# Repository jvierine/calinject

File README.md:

# Calinject

GPS-timed calibration bursts for SDR recordings: recover sample timing, estimate sample rate, and track frequency drift.

- **10 MHz harmonic comb**, with calibration harmonics through 70 MHz.
- **100 µs bursts by default**; pulse length and level adjustable over USB.
- Separate **10 MHz and 1 PPS SMA outputs**.
- **USB-C power**, firmware loading and status. Runs without a computer after programming; saved settings restore at startup.
- Four-layer, 90 × 65 mm PCB and a printable case with horizontal SMA ports.

Connect **antenna bias board → RF IN → TO SDR → receiver**. Add an active GPS antenna and 5 V USB-C power. The receiver path blocks DC and is specified for **0.5–70 MHz**, with about **3.2 dB loss**. Calibration leakage toward the antenna is finite; it must be measured on the first board.

Parts and board cost about **$80 per unit in small quantities**.

**Simulation, not measured performance:** longer bursts improve frequency estimation in the modeled receivers. Timing assumes known fixed delays and correctly associated UTC seconds. [Figures and assumptions](docs/figures.md).

[Download files](https://github.com/jvierine/calinject/releases) · [USB programming](firmware/README.md) · [Controls and LED](docs/operation.md) · [Print the case](mechanical/README.md) · [Hardware acceptance](docs/acceptance.md)

[Design](docs/design.md) · [Simulation details](docs/end-to-end.md) · [CAD/build](docs/build.md) · [Assembly](manufacturing/ASSEMBLY.md) · [Cost](docs/cost.md)

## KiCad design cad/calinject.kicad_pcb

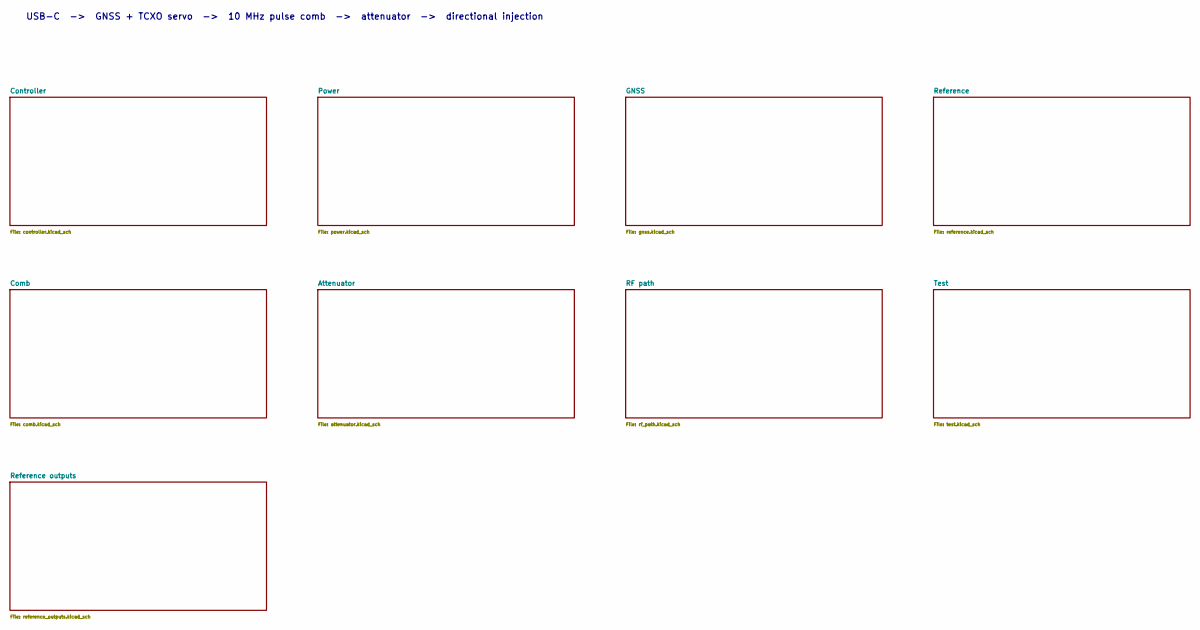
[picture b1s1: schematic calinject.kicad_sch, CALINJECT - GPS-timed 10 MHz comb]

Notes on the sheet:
USB-C -> GNSS + TCXO servo -> 10 MHz pulse comb -> attenuator -> directional injection

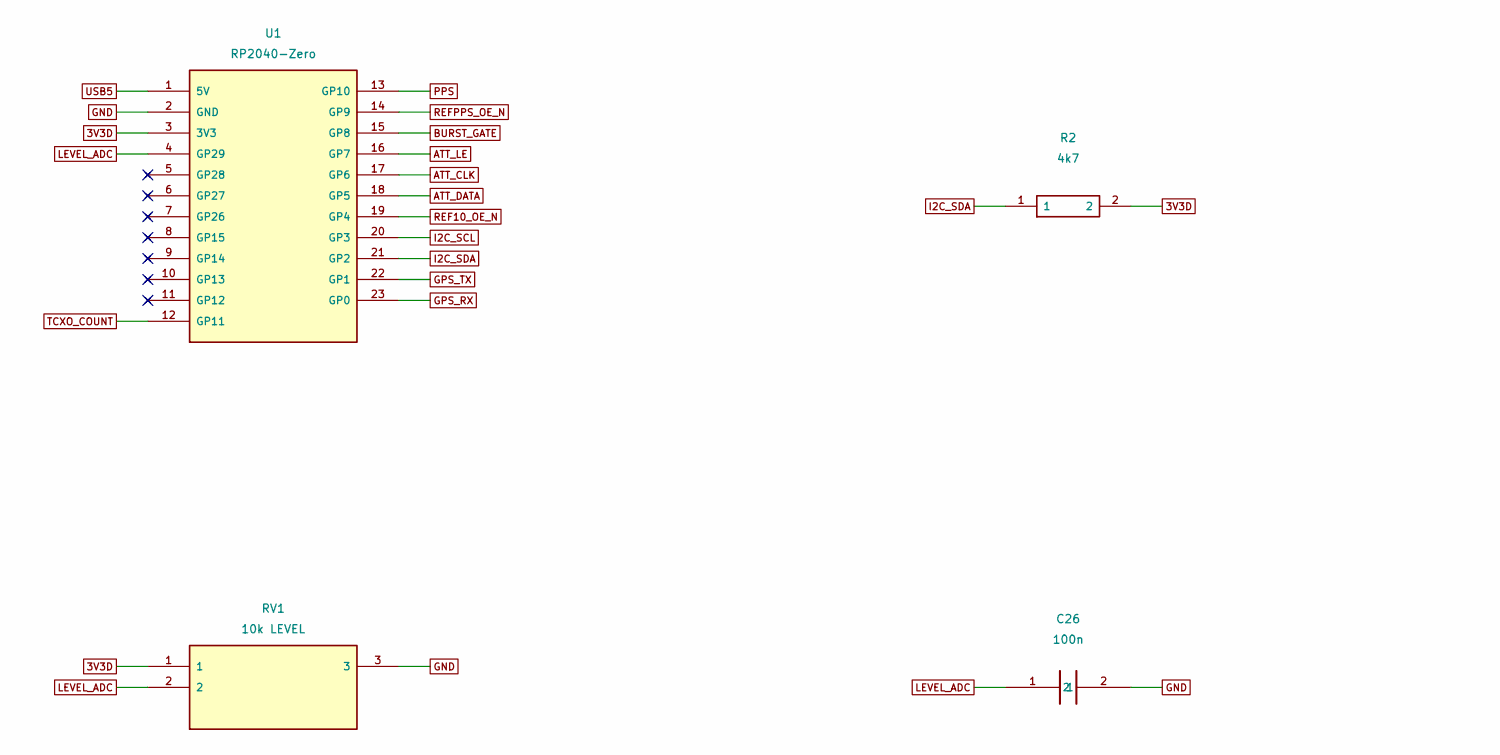
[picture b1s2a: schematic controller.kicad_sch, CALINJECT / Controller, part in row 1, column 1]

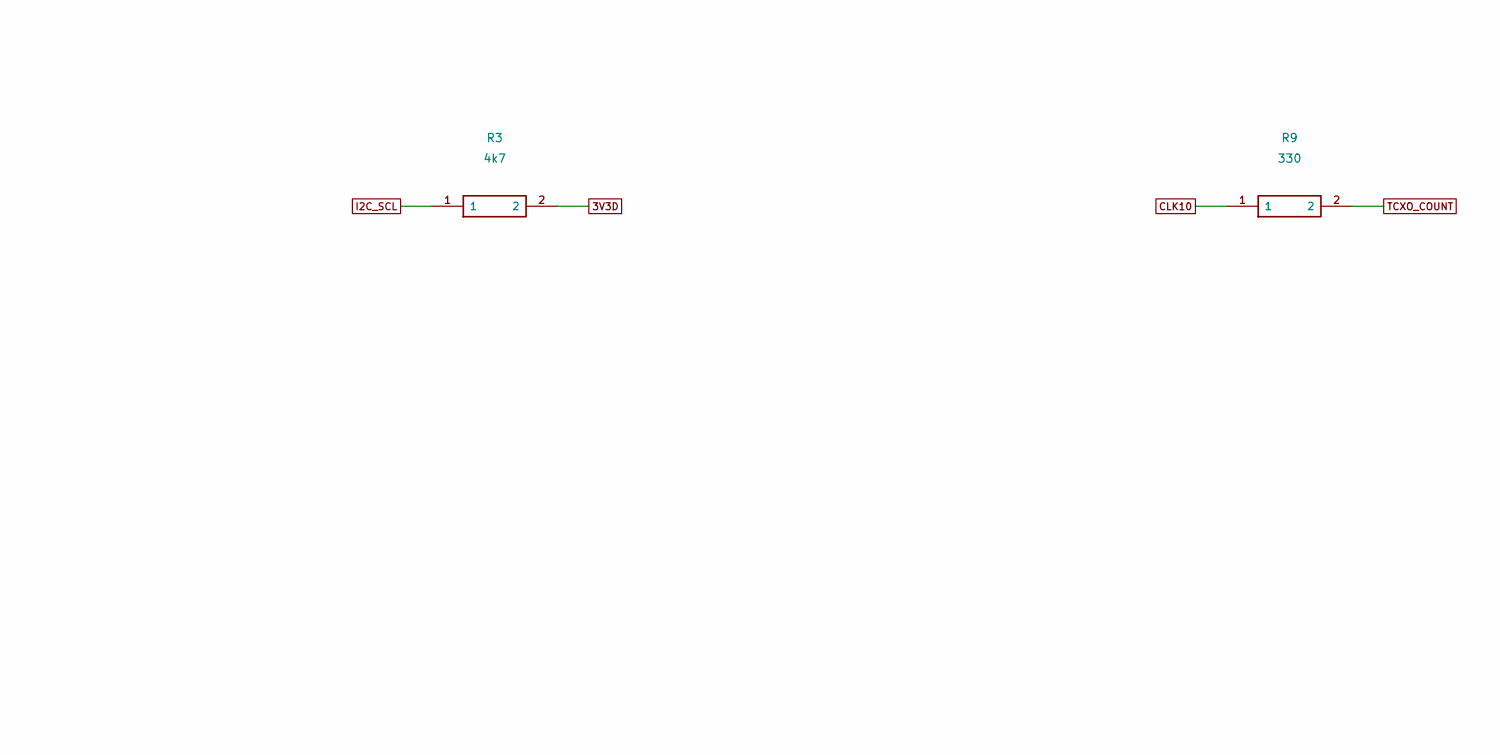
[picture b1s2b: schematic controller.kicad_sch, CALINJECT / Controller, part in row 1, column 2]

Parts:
C26: 100n; C_0603_C26
R2: 4k7; R_0603_R2
R3: 4k7; R_0603_R3
R9: 330; R_0603_R9
RV1: 10k LEVEL; Bourns_3362P_RV1
U1: RP2040-Zero; RP2040_Zero_U1

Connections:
3V3D: R2.2, R3.2, RV1.1, U1.3 (3V3)
ATT_CLK: U1.17 (GP6); also elsewhere on the board
ATT_DATA: U1.18 (GP5); also elsewhere on the board
ATT_LE: U1.16 (GP7); also elsewhere on the board
BURST_GATE: U1.15 (GP8); also elsewhere on the board
CLK10: R9.1; also elsewhere on the board
GND: C26.2, RV1.3, U1.2 (GND); also elsewhere on the board
GPS_RX: U1.23 (GP0); also elsewhere on the board
GPS_TX: U1.22 (GP1); also elsewhere on the board
I2C_SCL: R3.1, U1.20 (GP3); also elsewhere on the board
I2C_SDA: R2.1, U1.21 (GP2); also elsewhere on the board
LEVEL_ADC: C26.1, RV1.2, U1.4 (GP29)
PPS: U1.13 (GP10); also elsewhere on the board
REF10_OE_N: U1.19 (GP4); also elsewhere on the board
REFPPS_OE_N: U1.14 (GP9); also elsewhere on the board
TCXO_COUNT: R9.2, U1.12 (GP11); also elsewhere on the board
USB5: U1.1 (5V); also elsewhere on the board

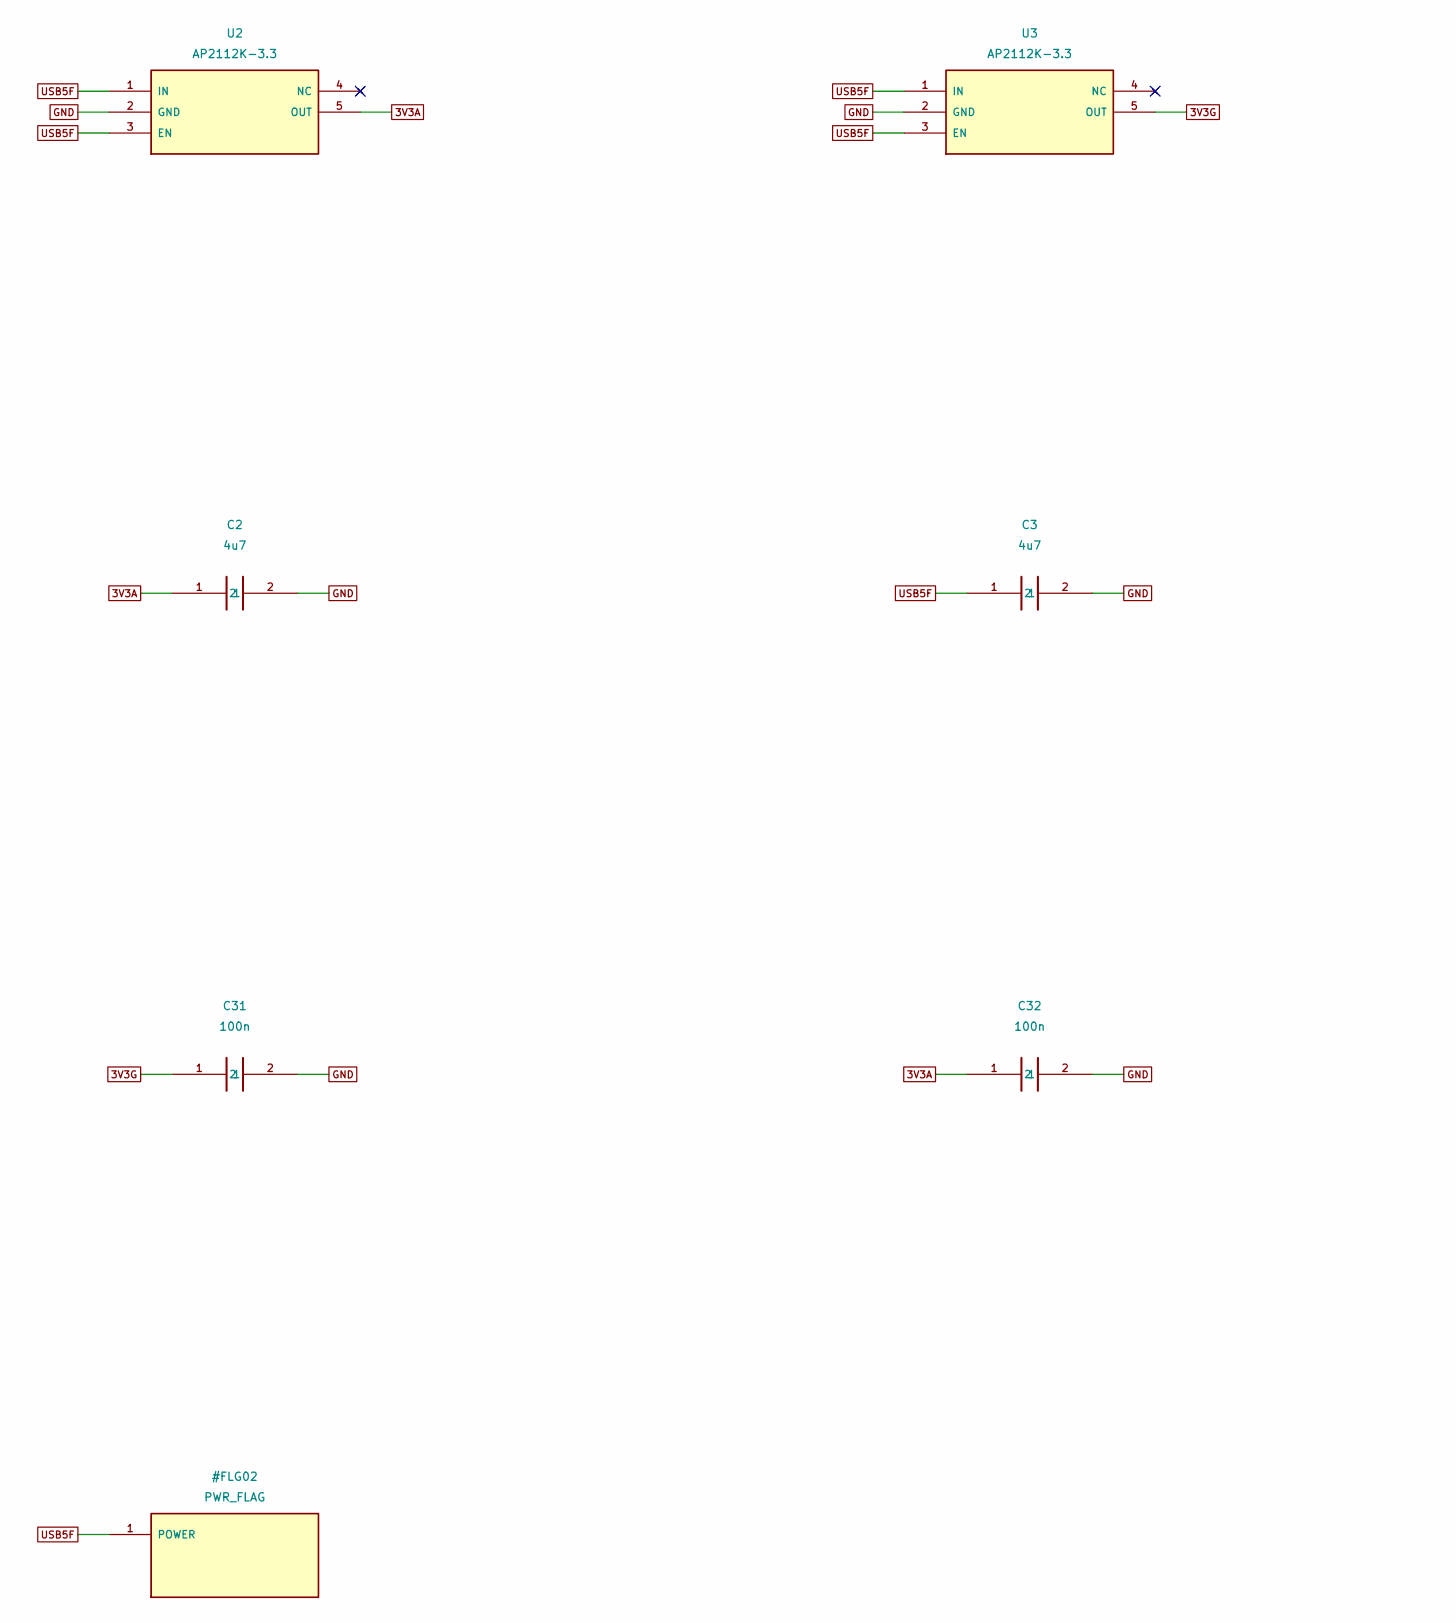
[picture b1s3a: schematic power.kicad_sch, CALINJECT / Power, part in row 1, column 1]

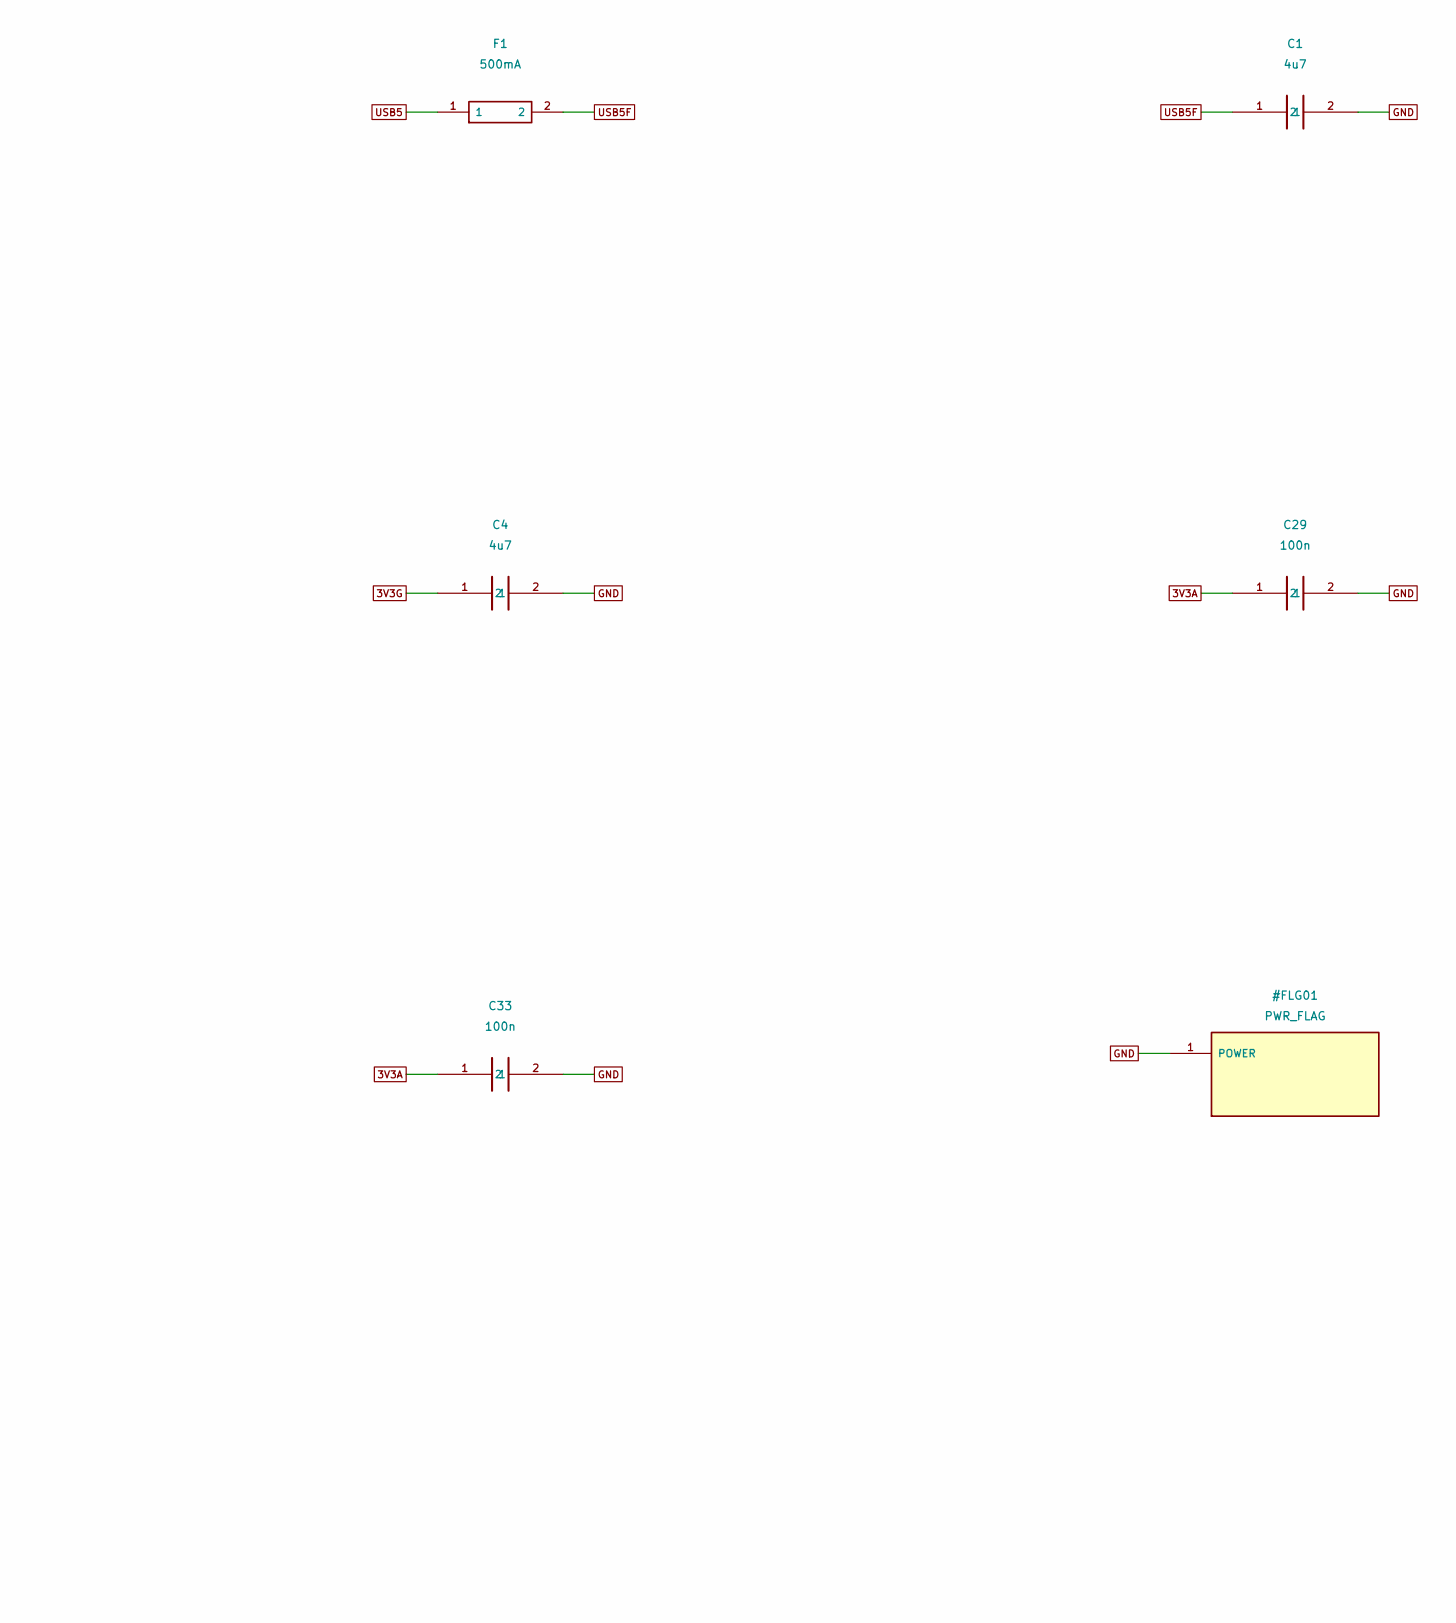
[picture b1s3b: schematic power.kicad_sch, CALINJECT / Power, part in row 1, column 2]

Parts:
C1: 4u7; C_0603_C1
C2: 4u7; C_0603_C2
C3: 4u7; C_0603_C3
C4: 4u7; C_0603_C4
C29: 100n; C_0603_C29
C31: 100n; C_0603_C31
C32: 100n; C_0603_C32
C33: 100n; C_0603_C33
F1: 500mA; F_1206_F1
U2: AP2112K-3.3; SOT23_5_U2
U3: AP2112K-3.3; SOT23_5_U3

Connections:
3V3A: C2.1, C29.1, C32.1, C33.1, U2.5 (OUT); also elsewhere on the board
3V3G: C4.1, C31.1, U3.5 (OUT); also elsewhere on the board
GND: C1.2, C2.2, C3.2, C4.2, C29.2, C31.2, C32.2, C33.2, U2.2 (GND), U3.2 (GND); also elsewhere on the board
USB5: F1.1; also elsewhere on the board
USB5F: C1.1, C3.1, F1.2, U2.1 (IN), U2.3 (EN), U3.1 (IN), U3.3 (EN)

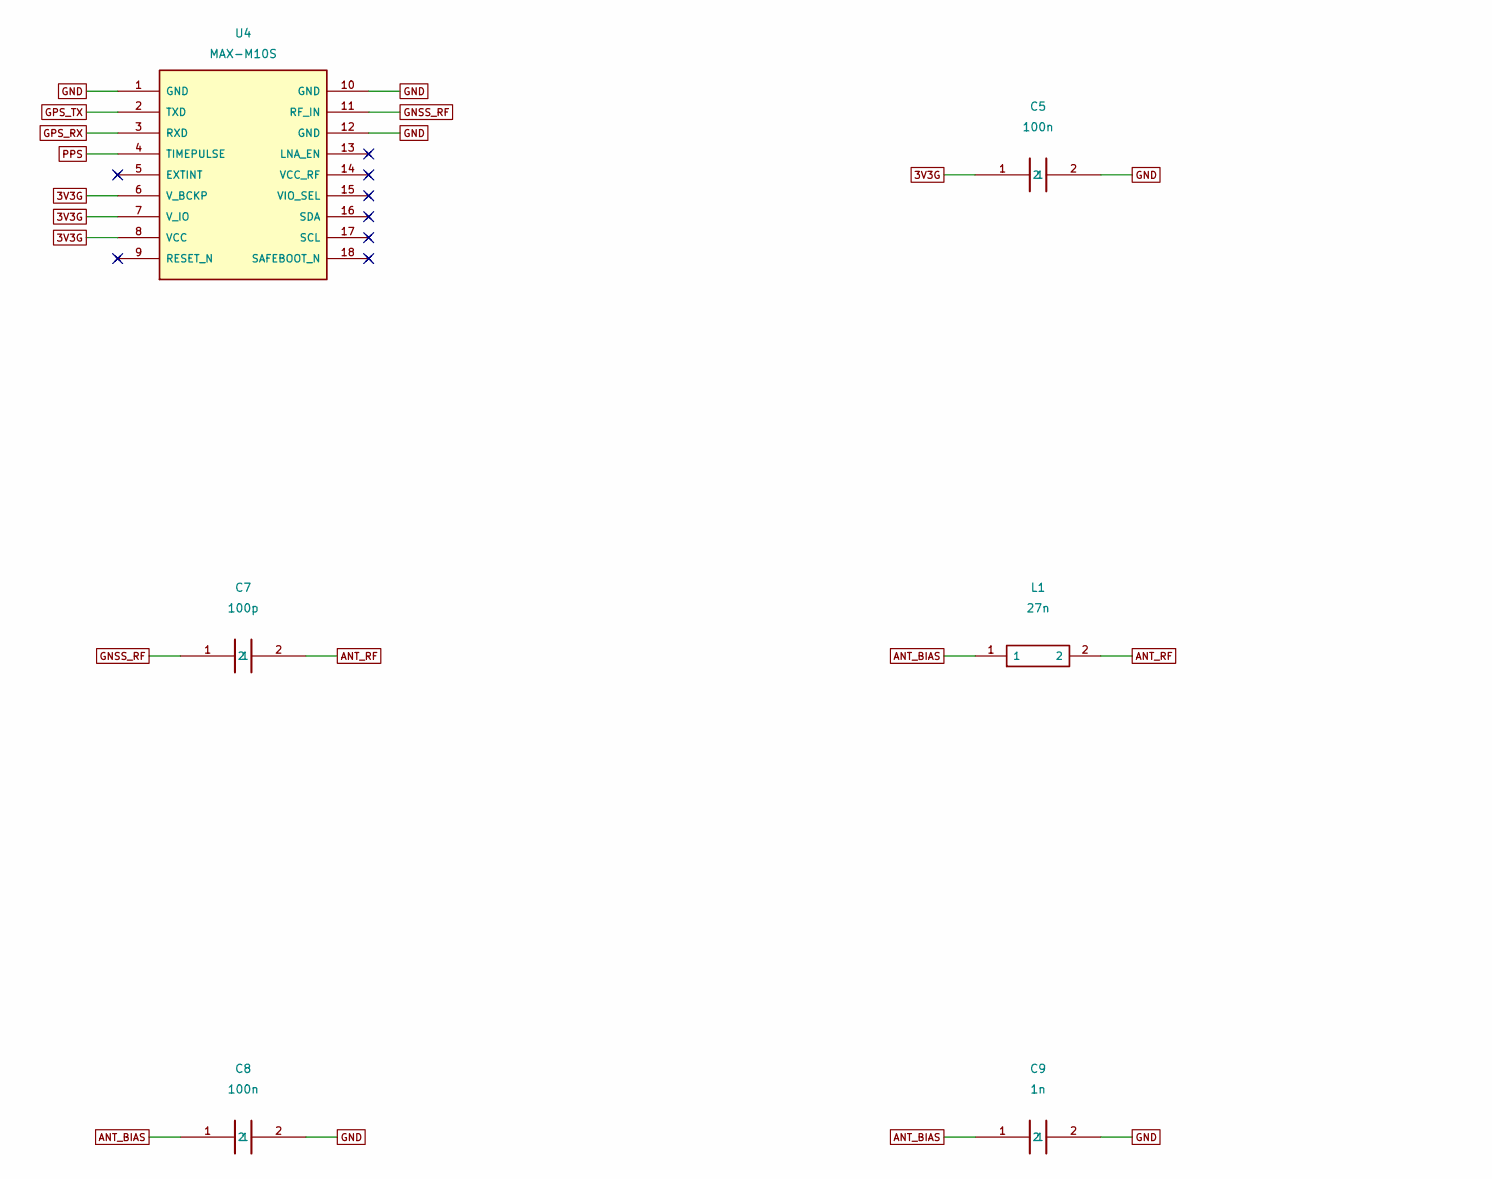
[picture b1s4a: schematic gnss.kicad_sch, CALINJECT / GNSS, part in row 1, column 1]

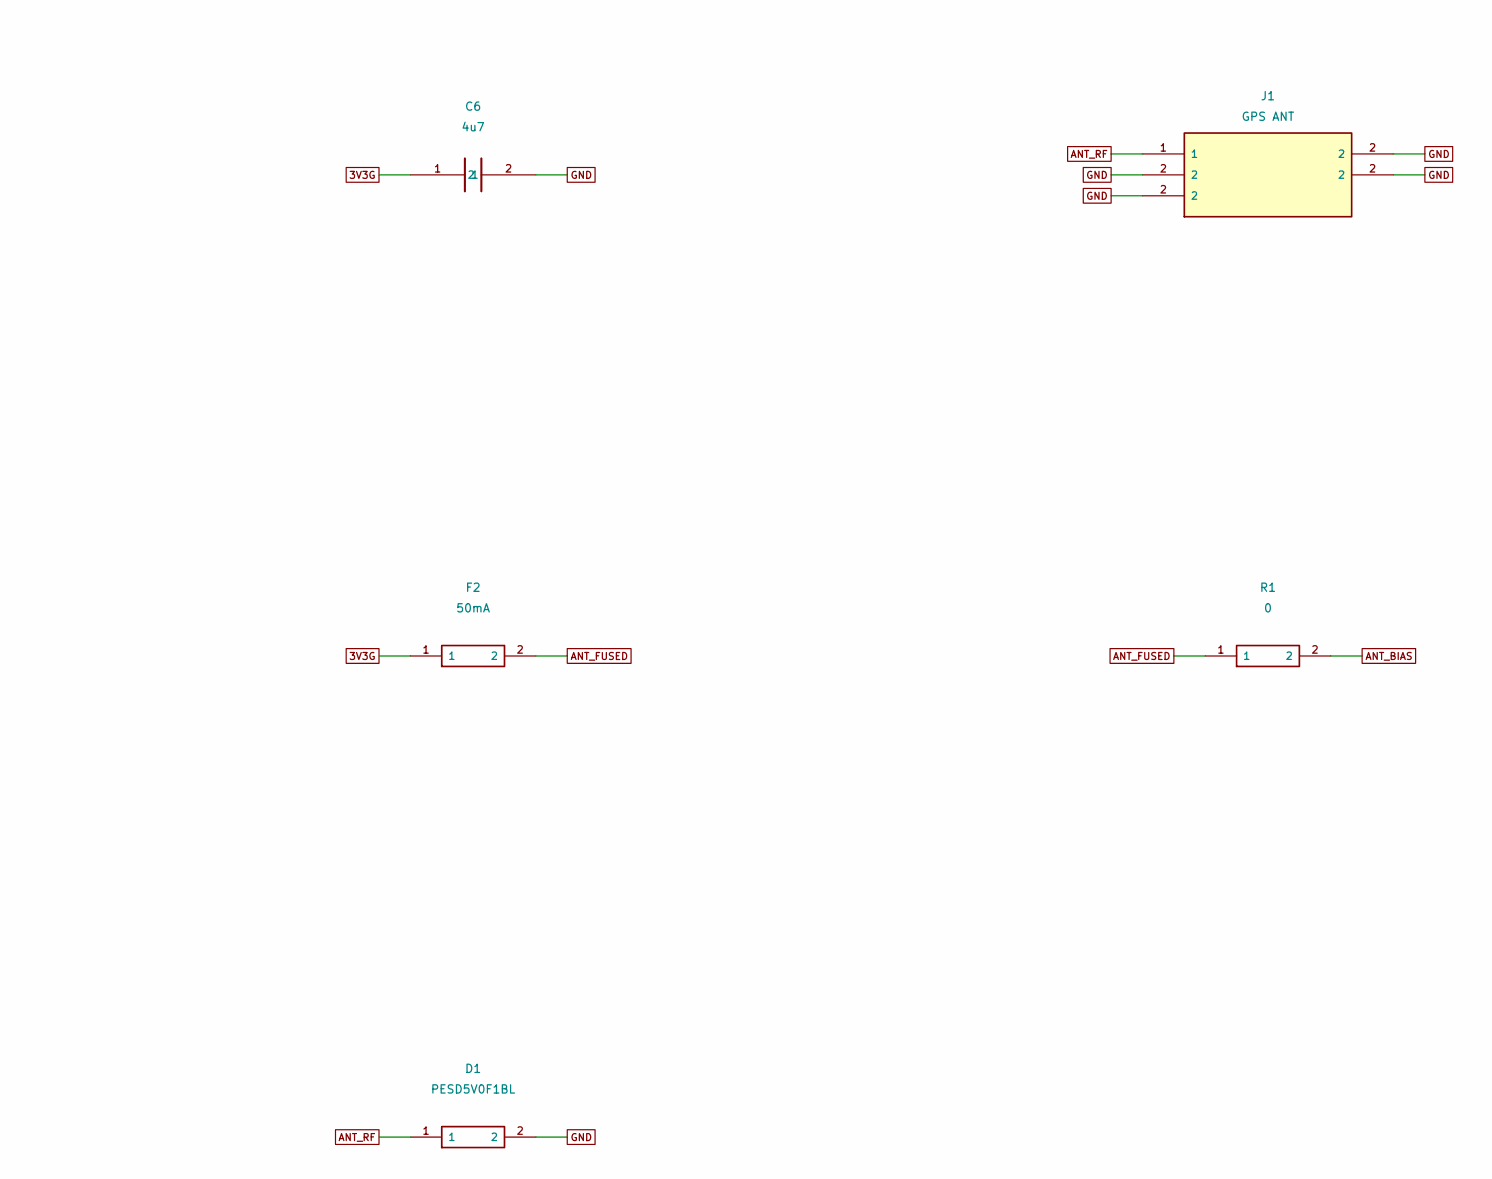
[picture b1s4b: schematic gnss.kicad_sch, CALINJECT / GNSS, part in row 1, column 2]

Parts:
C5: 100n; C_0603_C5
C6: 4u7; C_0603_C6
C7: 100p; C_0402_C7
C8: 100n; C_0603_C8
C9: 1n; C_0603_C9
D1: PESD5V0F1BL; DFN1006_2_D1
F2: 50mA; F_1206_F2
J1: GPS ANT; SMA_KWE_RA_J1
L1: 27n; L_0402_L1
R1: 0; R_0603_R1
U4: MAX-M10S; MAX_M10S_U4

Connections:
3V3G: C5.1, C6.1, F2.1, U4.6 (V_BCKP), U4.7 (V_IO), U4.8 (VCC); also elsewhere on the board
ANT_BIAS: C8.1, C9.1, L1.1, R1.2
ANT_FUSED: F2.2, R1.1
ANT_RF: C7.2, D1.1, J1.1, L1.2
GND: C5.2, C6.2, C8.2, C9.2, D1.2, J1.2, U4.1 (GND), U4.10 (GND), U4.12 (GND); also elsewhere on the board
GNSS_RF: C7.1, U4.11 (RF_IN)
GPS_RX: U4.3 (RXD); also elsewhere on the board
GPS_TX: U4.2 (TXD); also elsewhere on the board
PPS: U4.4 (TIMEPULSE); also elsewhere on the board

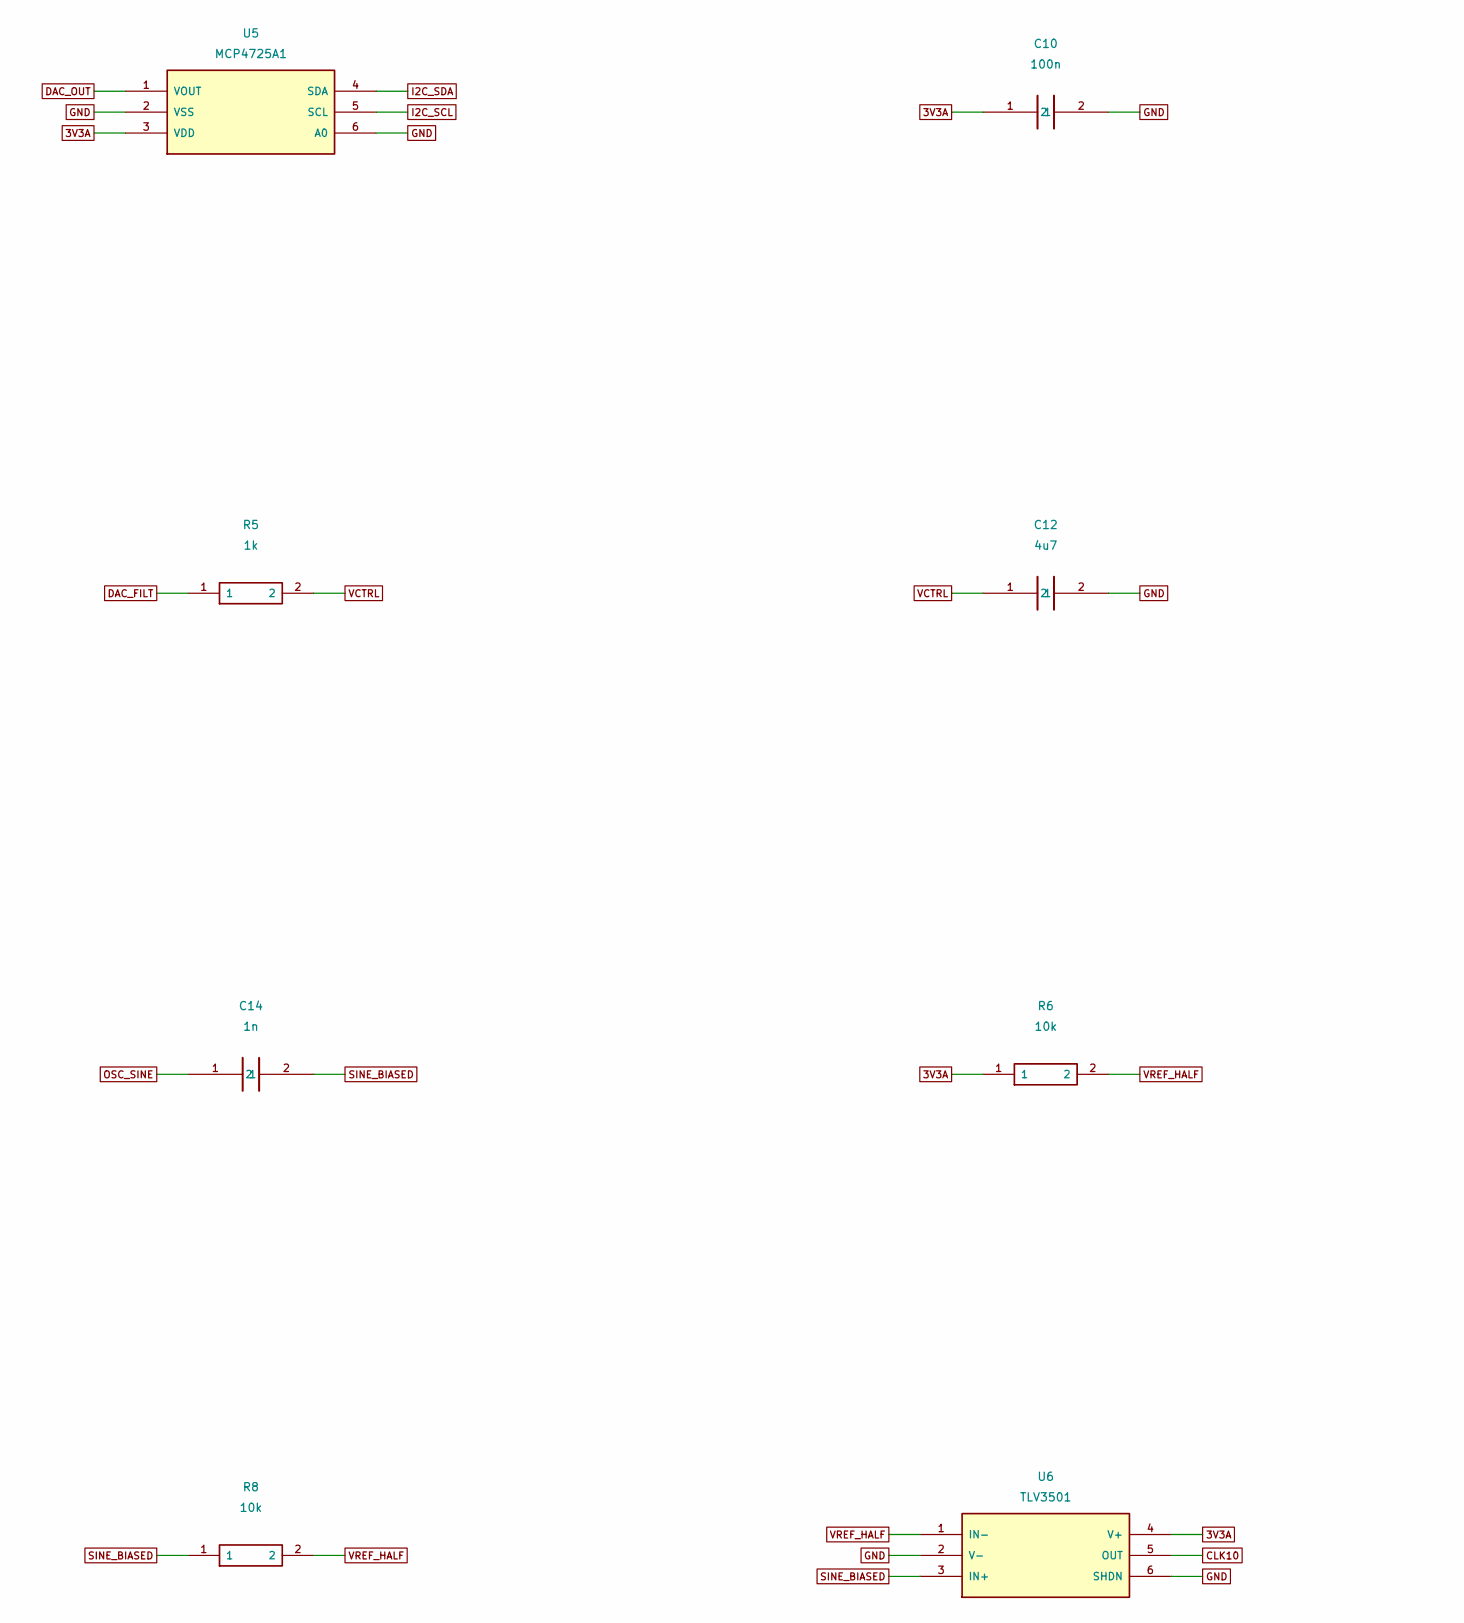
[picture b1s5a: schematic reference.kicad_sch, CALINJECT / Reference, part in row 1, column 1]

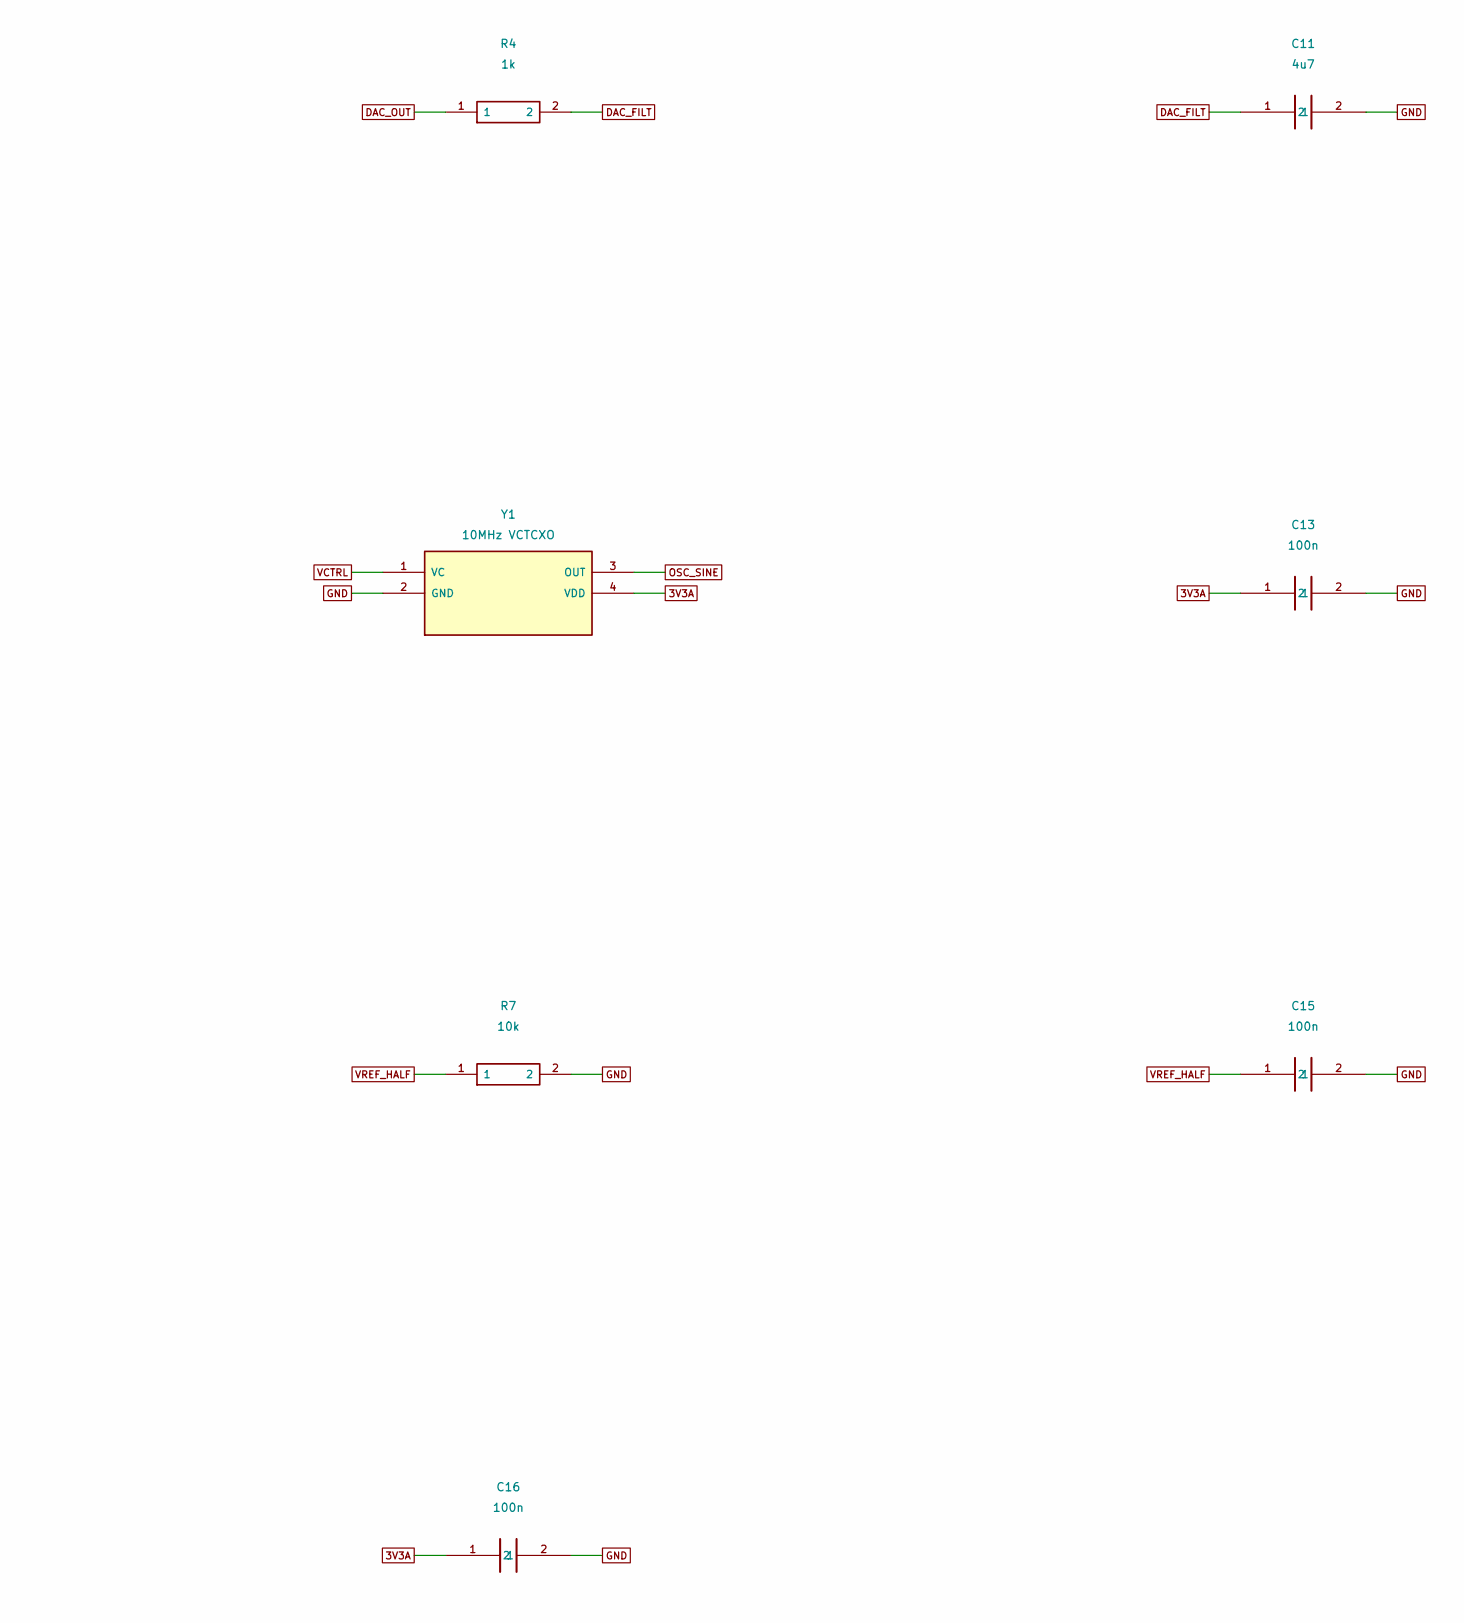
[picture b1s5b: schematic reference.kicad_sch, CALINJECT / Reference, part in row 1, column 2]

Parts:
C10: 100n; C_0603_C10
C11: 4u7; C_0603_C11
C12: 4u7; C_0603_C12
C13: 100n; C_0603_C13
C14: 1n; C_0603_C14
C15: 100n; C_0603_C15
C16: 100n; C_0603_C16
R4: 1k; R_0603_R4
R5: 1k; R_0603_R5
R6: 10k; R_0603_R6
R7: 10k; R_0603_R7
R8: 10k; R_0603_R8
U5: MCP4725A1; SOT23_6_U5
U6: TLV3501; SOT23_6_U6
Y1: 10MHz VCTCXO; KDS_DSA321SDN_Y1

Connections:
3V3A: C10.1, C13.1, C16.1, R6.1, U5.3 (VDD), U6.4 (V+), Y1.4 (VDD); also elsewhere on the board
CLK10: U6.5 (OUT); also elsewhere on the board
DAC_FILT: C11.1, R4.2, R5.1
DAC_OUT: R4.1, U5.1 (VOUT)
GND: C10.2, C11.2, C12.2, C13.2, C15.2, C16.2, R7.2, U5.2 (VSS), U5.6 (A0), U6.2 (V-), U6.6 (SHDN), Y1.2 (GND); also elsewhere on the board
I2C_SCL: U5.5 (SCL); also elsewhere on the board
I2C_SDA: U5.4 (SDA); also elsewhere on the board
OSC_SINE: C14.1, Y1.3 (OUT)
SINE_BIASED: C14.2, R8.1, U6.3 (IN+)
VCTRL: C12.1, R5.2, Y1.1 (VC); also elsewhere on the board
VREF_HALF: C15.1, R6.2, R7.1, R8.2, U6.1 (IN-)

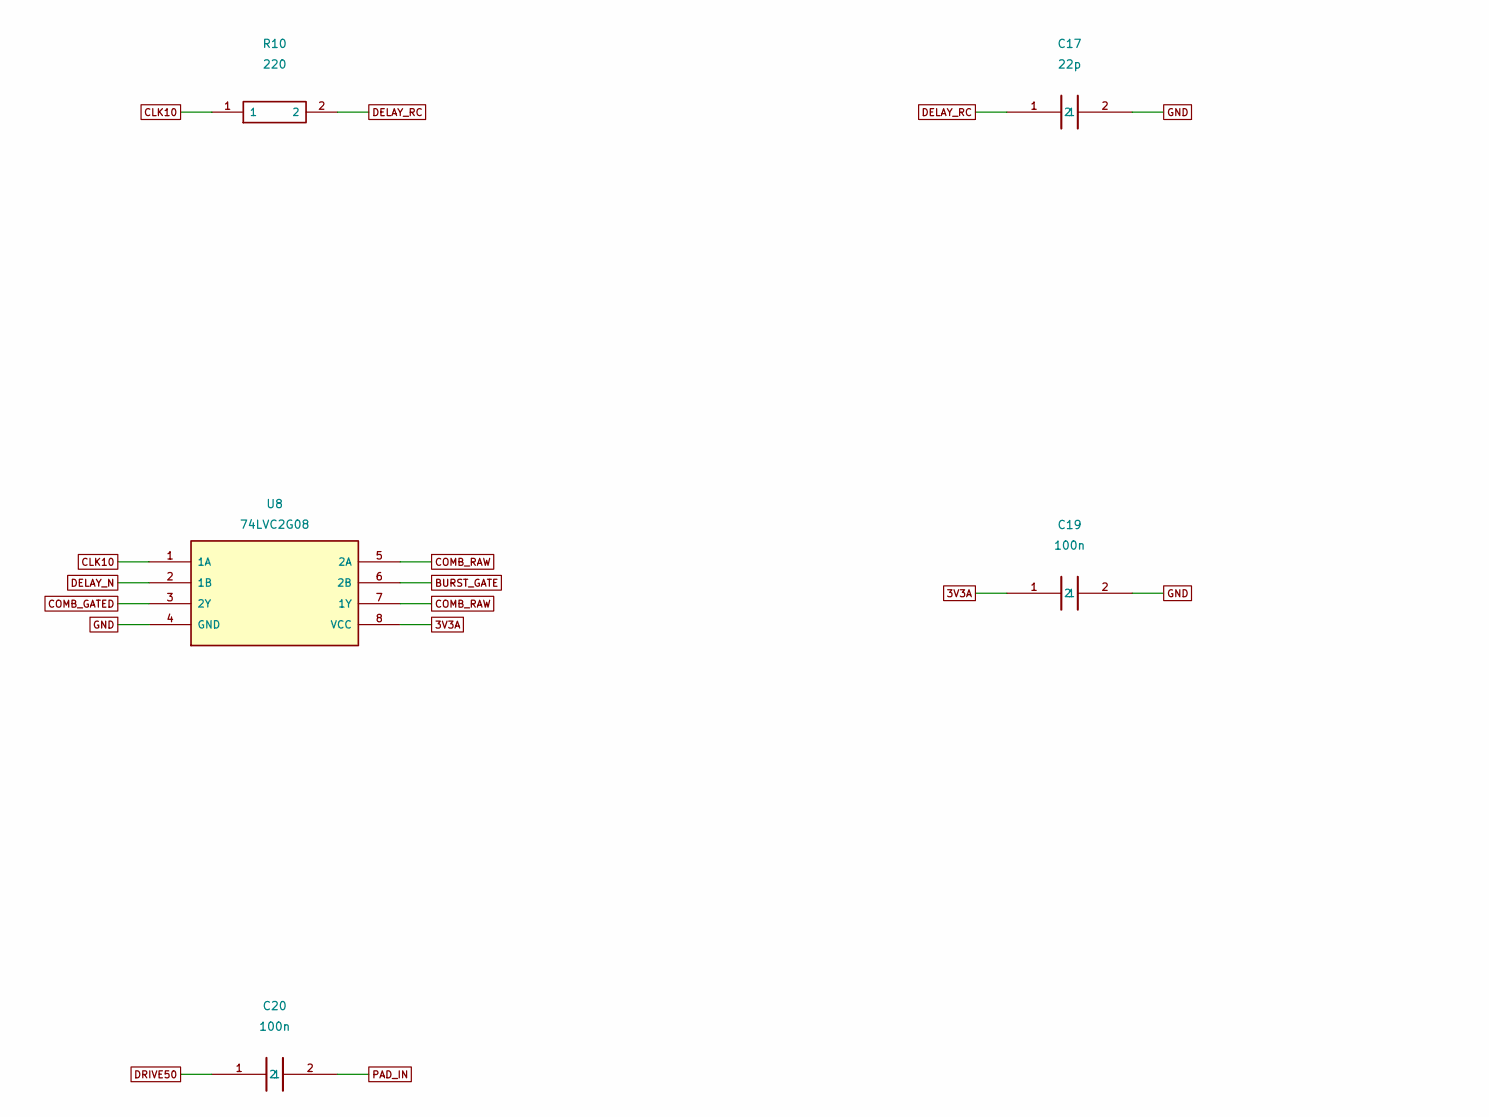
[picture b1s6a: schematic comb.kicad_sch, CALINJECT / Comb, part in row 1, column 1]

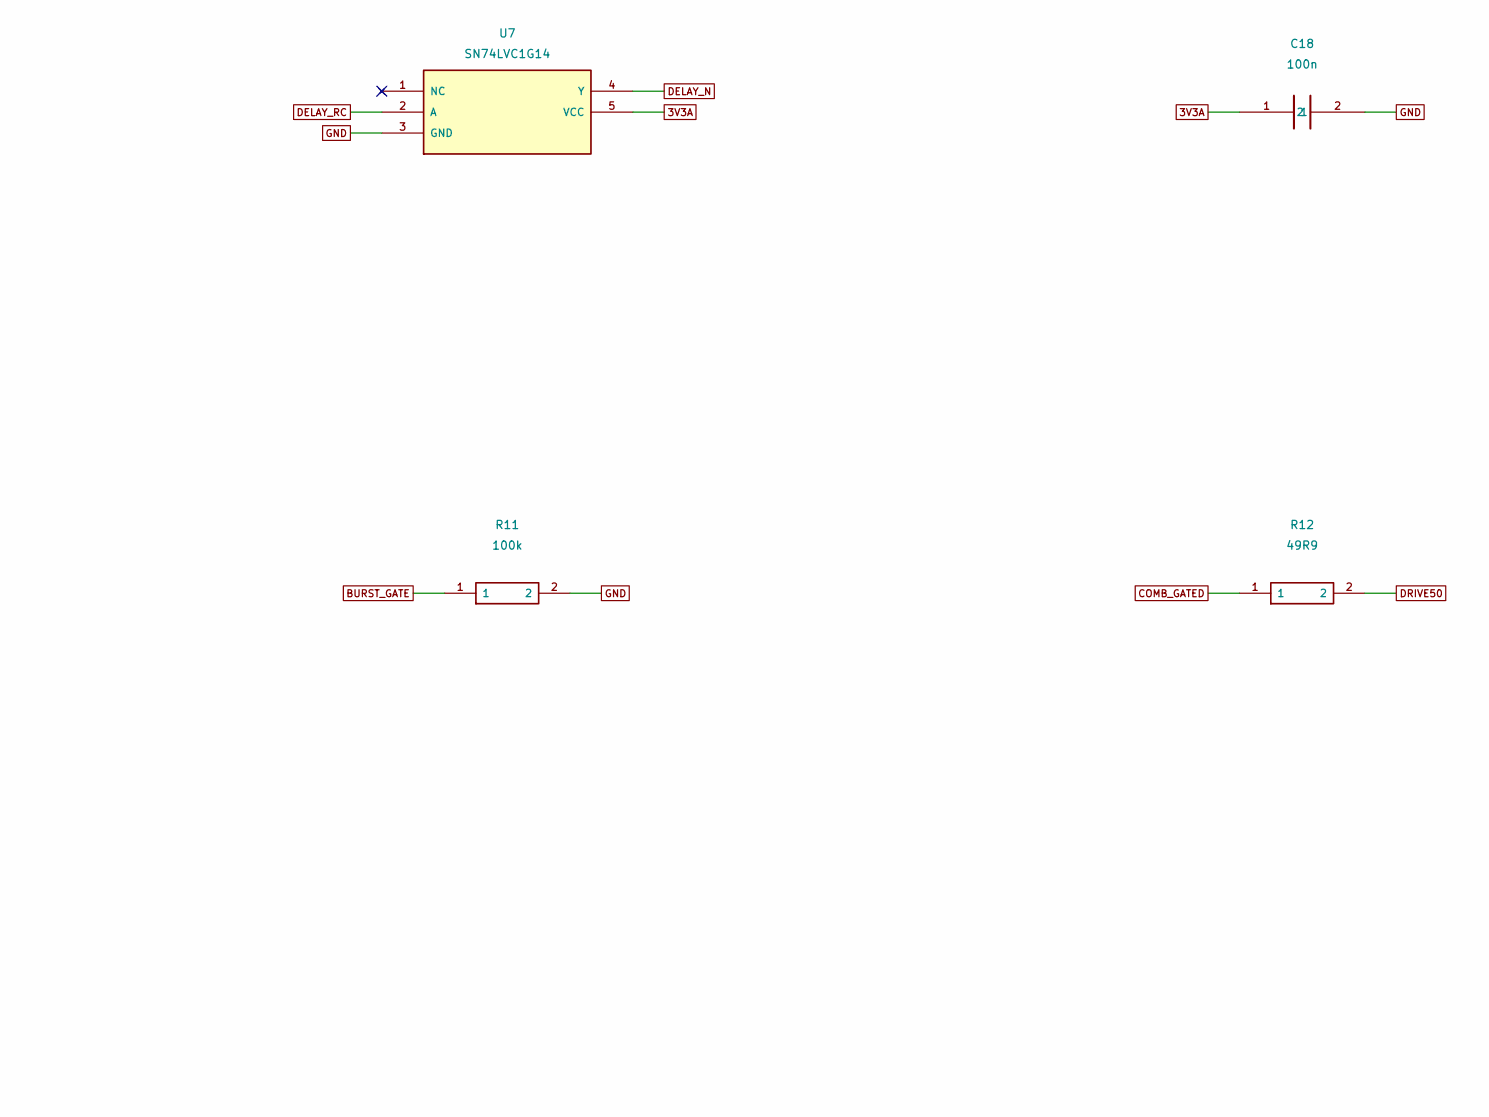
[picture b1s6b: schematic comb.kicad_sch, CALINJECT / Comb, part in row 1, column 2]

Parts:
C17: 22p; C_0603_C17
C18: 100n; C_0603_C18
C19: 100n; C_0603_C19
C20: 100n; C_0603_C20
R10: 220; R_0603_R10
R11: 100k; R_0603_R11
R12: 49R9; R_0603_R12
U7: SN74LVC1G14; SOT23_5_U7
U8: 74LVC2G08; VSSOP8_DCU_U8

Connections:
3V3A: C18.1, C19.1, U7.5 (VCC), U8.8 (VCC); also elsewhere on the board
BURST_GATE: R11.1, U8.6 (2B); also elsewhere on the board
CLK10: R10.1, U8.1 (1A); also elsewhere on the board
COMB_GATED: R12.1, U8.3 (2Y)
COMB_RAW: U8.5 (2A), U8.7 (1Y)
DELAY_N: U7.4 (Y), U8.2 (1B)
DELAY_RC: C17.1, R10.2, U7.2 (A)
DRIVE50: C20.1, R12.2
GND: C17.2, C18.2, C19.2, R11.2, U7.3 (GND), U8.4 (GND); also elsewhere on the board
PAD_IN: C20.2; also elsewhere on the board
